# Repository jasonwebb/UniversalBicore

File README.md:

UniversalBicore
===============

Circuit board to make it easier to work with bicore-based BEAM circuits

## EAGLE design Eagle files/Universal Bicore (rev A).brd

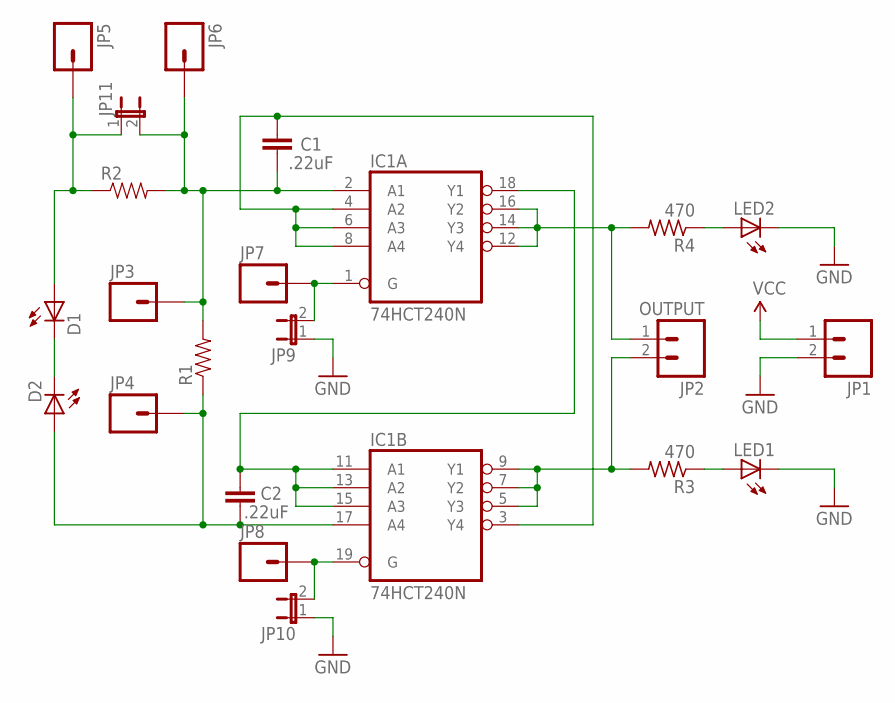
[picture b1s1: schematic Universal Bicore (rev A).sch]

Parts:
C1, C2: .22uF; CAP-PTH-SMALLEZ
D1, D2: LED3MM
IC1: 74HCT240N; DIL20
JP1: M02PTH; 1X02
JP2: OUTPUT; 1X02
JP3, JP4, JP5, JP6, JP7, JP8: M01PTH; 1X01
JP9, JP10, JP11: JUMPER-2SMD-NC; SJ_2S
LED1, LED2: LEDCHIPLED_0805; CHIPLED_0805
R1, R2: RESISTOREZ; AXIAL-0.3EZ
R3, R4: 470; R0805

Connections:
GND: IC1.10 (GND), JP1.2, JP9.1, JP10.1, LED1.C, LED2.C
unnamed: C1.1, IC1.2 (A1), JP3.1, JP6.1, JP11.2, R1.P$2 (2), R2.P$2 (2)
unnamed: C1.2, IC1.3 (Y4), IC1.4 (A2), IC1.6 (A3), IC1.8 (A4)
unnamed: IC1.12 (Y4), IC1.14 (Y3), IC1.16 (Y2), JP2.1, R4.2
unnamed: C2.1, IC1.11 (A1), IC1.13 (A2), IC1.15 (A3), IC1.18 (Y1)
unnamed: C2.2, D2.A, IC1.17 (A4), JP4.1, R1.P$1 (1)
unnamed: IC1.5 (Y3), IC1.7 (Y2), IC1.9 (Y1), JP2.2, R3.2
unnamed: D1.A, JP5.1, JP11.1, R2.P$1 (1)
unnamed: D1.K (C), D2.K (C)
unnamed: LED2.A, R4.1
unnamed: LED1.A, R3.1
unnamed: IC1.1 (G), JP7.1, JP9.2
unnamed: IC1.19 (G), JP8.1, JP10.2
VCC: IC1.20 (VCC), JP1.1

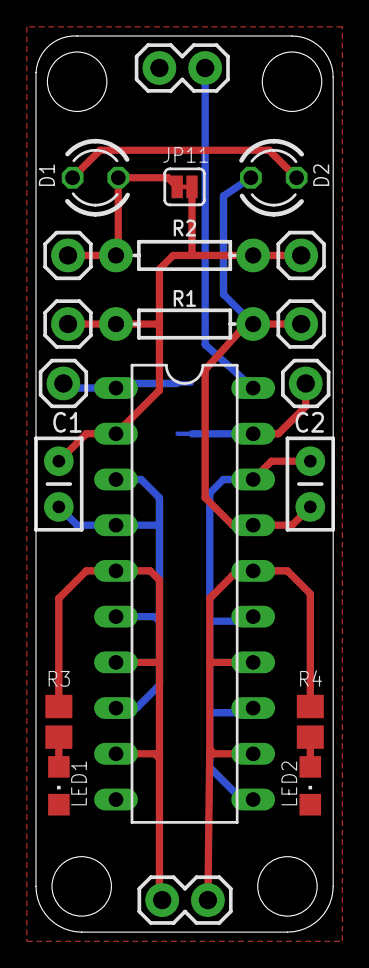
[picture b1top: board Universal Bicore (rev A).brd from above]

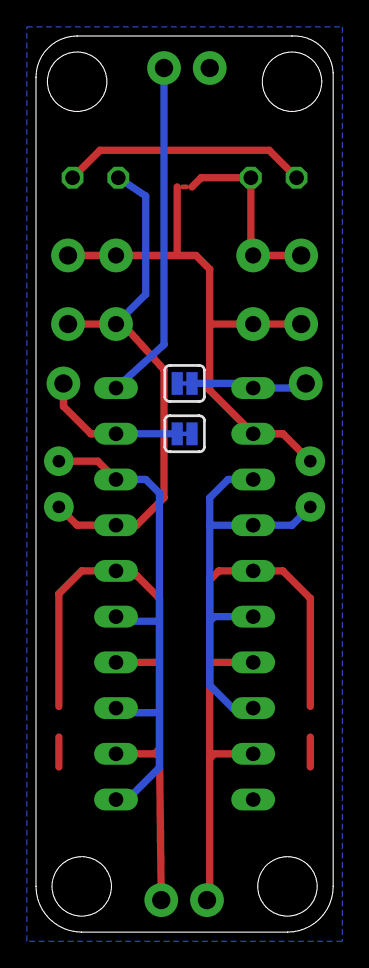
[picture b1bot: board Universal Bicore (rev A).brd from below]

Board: 4 copper layers, 16.5 x 49.8 mm, 22 parts (2 on the bottom side), 14 nets.

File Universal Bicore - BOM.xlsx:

ID | Value | Package | Qty | Cost | Total | Part number | Source
IC1 | 74HCT240 | 20-PDIP | 1 | 0.59 | 0.59 | 296-8399-5-ND | http://www.digikey.com/product-detail/en/SN74HCT240N/296-839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
- | 20-pin IC socket |  | 1 | 0.31 | 0.31 | A100208-ND | http://www.digikey.com/product-detail/en/1-390261-6/A100208-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
R1 | 100k to 10M | Axial, through-hole | 1 | 0 | 0 |  | Assortment on hand
R2 | Less than R1 | Axial, through-hole | 1 | 0 | 0 |  | Assortment on hand
R3-R4 | 470 | 0805 | 2 | 0.1 | 0.2 | P470ACT-ND | http://www.digikey.com/product-detail/en/ERJ-6GEYJ471V/P470A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
C1-C2 | .22uF | Radial, through-hole | 2 | 0.28999999999999998 | 0.57999999999999996 | 445-2849-ND | http://www.digikey.com/product-detail/en/FK28X7R1C224K/445-2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
D1-D2 | SFH 205 F | Radial, through-hole | 2 | 0.83 | 1.66 | 475-1429-ND | http://www.digikey.com/product-detail/en/SFH%20205%20F/475-1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
LED1-LED2 | Blue | 0805 | 2 | 0.43 | 0.86 | 160-1645-1-ND | http://www.digikey.com/product-detail/en/LTST-C171TBKT/160-1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
 |  |  |  | Total | 4.2

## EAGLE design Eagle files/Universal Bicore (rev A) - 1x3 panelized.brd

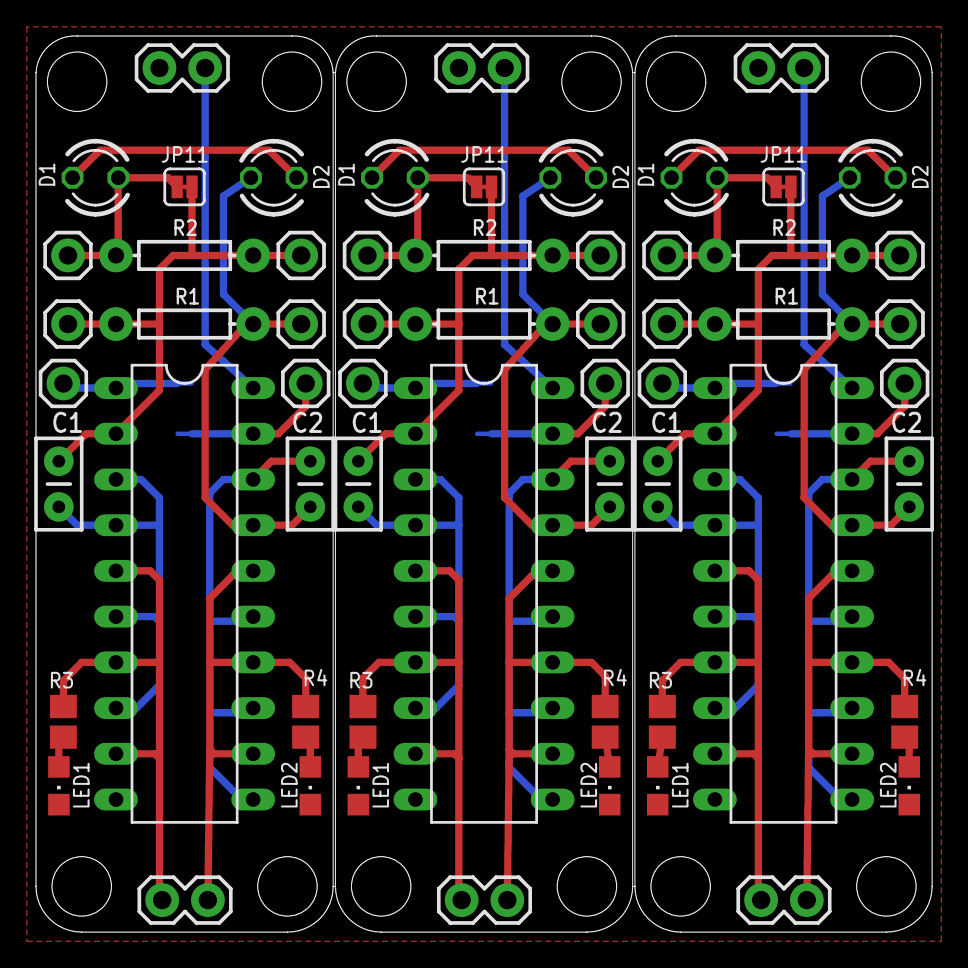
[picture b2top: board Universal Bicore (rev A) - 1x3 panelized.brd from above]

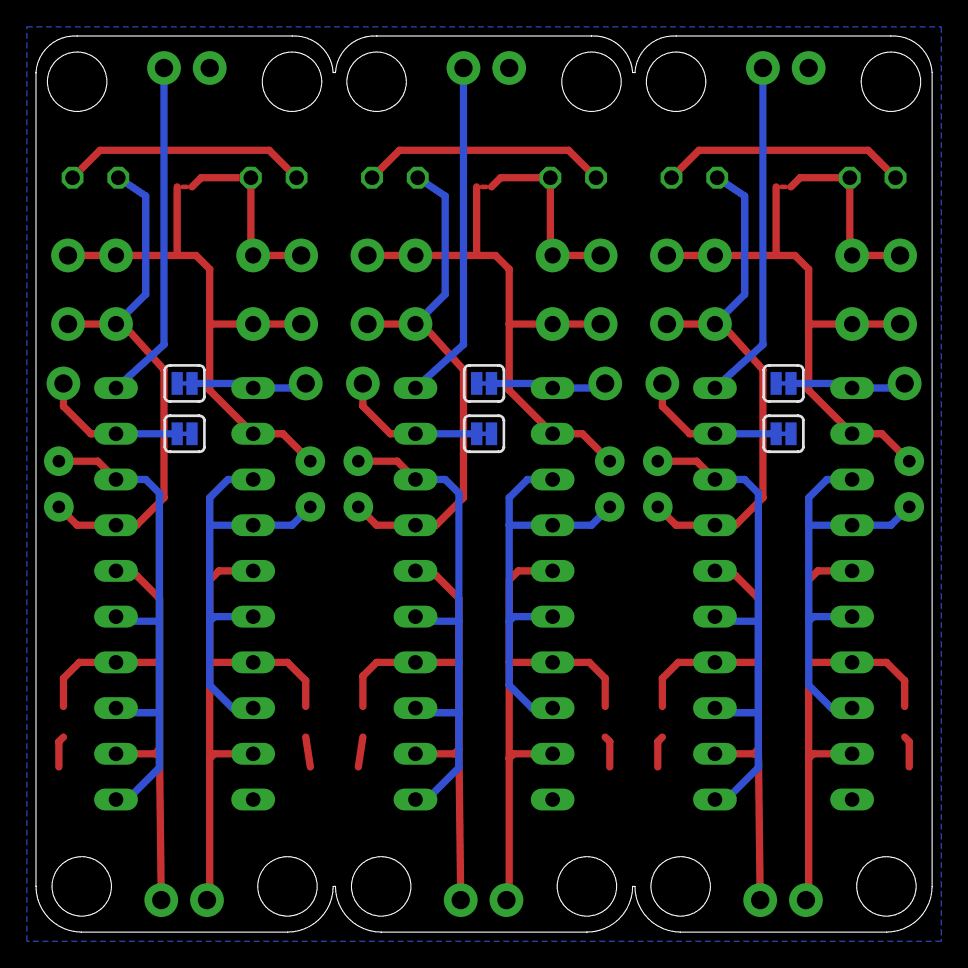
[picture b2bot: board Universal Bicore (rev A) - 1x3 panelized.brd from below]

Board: 4 copper layers, 49.8 x 49.8 mm, 66 parts (6 on the bottom side), 40 nets.

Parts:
C1, C2, C3, C4, C5, C6: .22uF; CAP-PTH-SMALLEZ
D1, D2, D3, D4, D5, D6: LED3MM
IC1, IC2, IC3: 74HCT240N; DIL20
JP1, JP12, JP23: 1X02
JP2, JP13, JP24: OUTPUT; 1X02
JP3, JP4, JP5, JP6, JP7, JP8, JP14, JP15, JP16, JP17, JP18, JP19, JP25, JP26, JP27, JP28, JP29, JP30: 1X01
JP9, JP10, JP11, JP20, JP21, JP22, JP31, JP32, JP33: SJ_2S
LED1, LED2, LED3, LED4, LED5, LED6: CHIPLED_0805
R1, R2, R5, R6, R9, R10: AXIAL-0.3EZ
R3, R4, R7, R8, R11, R12: 470; R0805

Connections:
GND: IC1.10, IC2.10, IC3.10, JP1.2, JP9.1, JP10.1, JP12.2, JP20.1, JP21.1, JP23.2, JP31.1, JP32.1, LED1.C, LED2.C, LED3.C, LED4.C, LED5.C, LED6.C
unnamed: C1.1, IC1.2, JP3.1, JP6.1, JP11.2, R1.P$2, R2.P$2
unnamed: C1.2, IC1.3, IC1.4, IC1.6, IC1.8
unnamed: IC1.12, IC1.14, IC1.16, JP2.1, R4.2
unnamed: C2.1, IC1.11, IC1.13, IC1.15, IC1.18
unnamed: C2.2, D2.A, IC1.17, JP4.1, R1.P$1
unnamed: IC1.5, IC1.7, IC1.9, JP2.2, R3.2
unnamed: D1.A, JP5.1, JP11.1, R2.P$1
unnamed: D1.K, D2.K
unnamed: LED2.A, R4.1
unnamed: LED1.A, R3.1
unnamed: IC1.1, JP7.1, JP9.2
unnamed: IC1.19, JP8.1, JP10.2
unnamed: C3.1, IC2.2, JP14.1, JP17.1, JP22.2, R5.P$2, R6.P$2
unnamed: C3.2, IC2.3, IC2.4, IC2.6, IC2.8
unnamed: C4.1, IC2.11, IC2.13, IC2.15, IC2.18
unnamed: C4.2, D4.A, IC2.17, JP15.1, R5.P$1
unnamed: IC2.12, IC2.14, IC2.16, JP13.1, R8.2
unnamed: IC2.5, IC2.7, IC2.9, JP13.2, R7.2
unnamed: D3.A, JP16.1, JP22.1, R6.P$1
unnamed: D3.K, D4.K
unnamed: LED4.A, R8.1
unnamed: LED3.A, R7.1
unnamed: IC2.19, JP19.1, JP21.2
unnamed: IC2.1, JP18.1, JP20.2
unnamed: C5.1, IC3.2, JP25.1, JP28.1, JP33.2, R9.P$2, R10.P$2
unnamed: C5.2, IC3.3, IC3.4, IC3.6, IC3.8
unnamed: C6.1, IC3.11, IC3.13, IC3.15, IC3.18
unnamed: C6.2, D6.A, IC3.17, JP26.1, R9.P$1
unnamed: IC3.12, IC3.14, IC3.16, JP24.1, R12.2
unnamed: IC3.5, IC3.7, IC3.9, JP24.2, R11.2
unnamed: D5.A, JP27.1, JP33.1, R10.P$1
unnamed: D5.K, D6.K
unnamed: LED6.A, R12.1
unnamed: LED5.A, R11.1
unnamed: IC3.19, JP30.1, JP32.2
unnamed: IC3.1, JP29.1, JP31.2
VCC: IC1.20, JP1.1
VCC1: IC2.20, JP12.1
VCC2: IC3.20, JP23.1

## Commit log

2013-12-17 Initial commit
    BOM, Eagle files and Gerbers
2013-12-24 Updated panelized PCB
    Fixed ground bug in panelized PCB.

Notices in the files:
parts and their libraries:
SparkFun-Capacitors: Licensing: CC v3.0 Share-Alike You are welcome to use this library for commercial purposes.
